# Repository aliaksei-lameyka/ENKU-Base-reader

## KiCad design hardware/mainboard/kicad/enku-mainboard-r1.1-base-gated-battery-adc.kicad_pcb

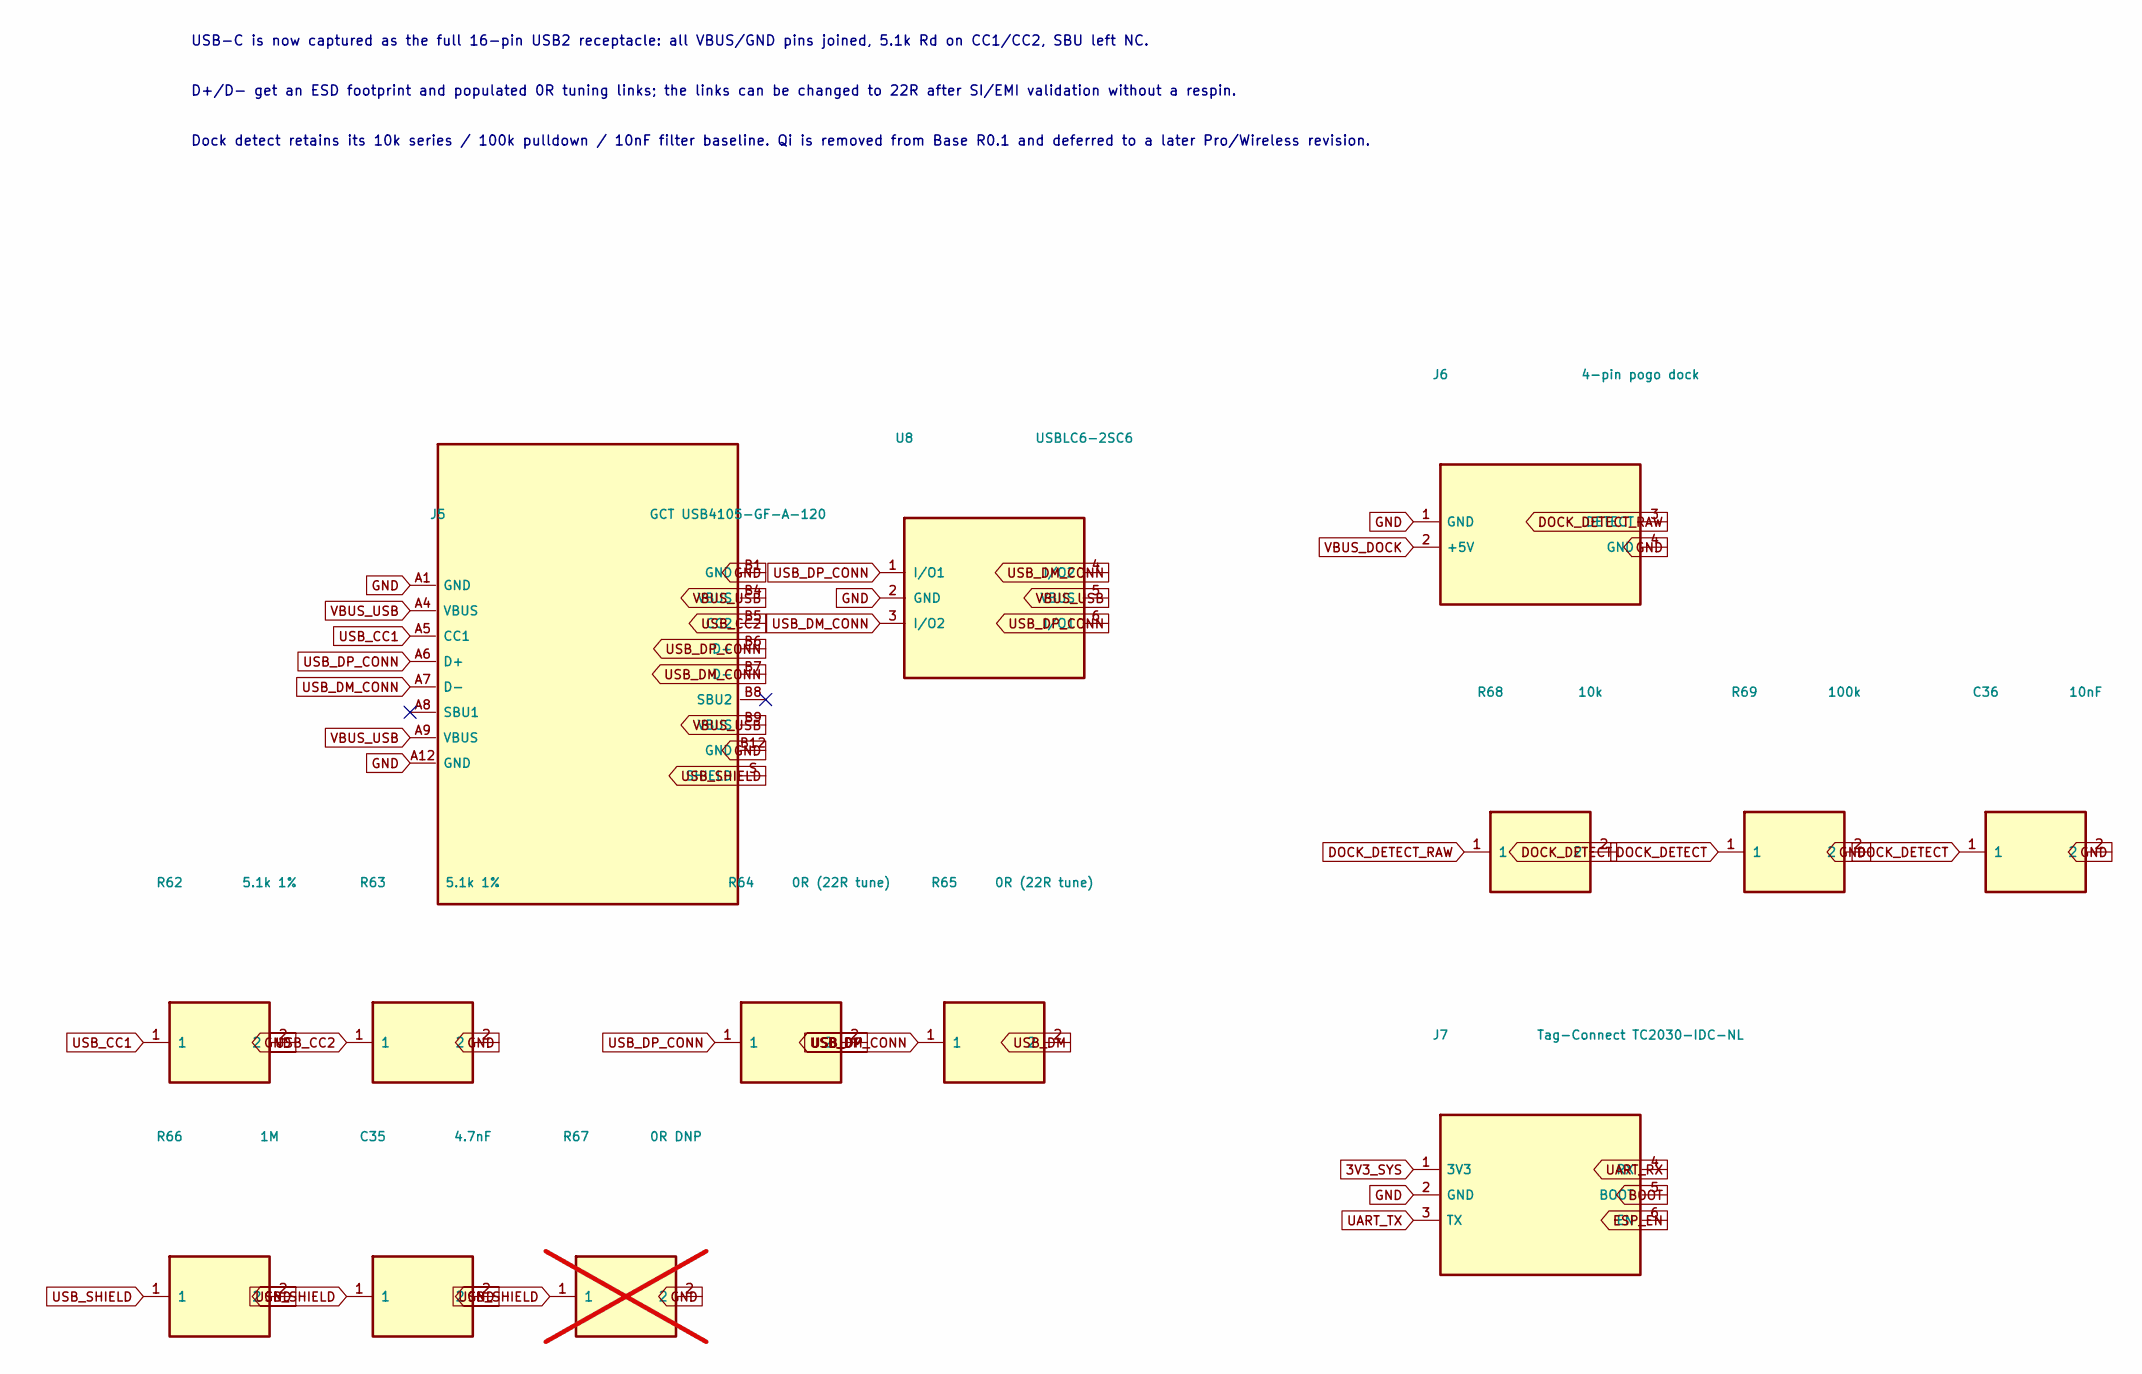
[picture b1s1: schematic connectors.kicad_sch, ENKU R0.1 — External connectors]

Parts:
C35: 4.7nF; C_0603_1608Metric
C36: 10nF; C_0603_1608Metric
J5: GCT USB4105-GF-A-120; USB_C_Receptacle_GCT_USB4105-xx-A_16P_TopMnt_Horizontal
J6: 4-pin pogo dock; DOCK_POGO_4
J7: Tag-Connect TC2030-IDC-NL; Tag-Connect_TC2030-IDC-NL_2x03_P1.27mm_Vertical
R62, R63: 5.1k 1%; R_0603_1608Metric
R64, R65: 0R (22R tune); R_0603_1608Metric
R66: 1M; R_0603_1608Metric
R67: 0R DNP; R_0603_1608Metric; not fitted
R68: 10k; R_0603_1608Metric
R69: 100k; R_0603_1608Metric
U8: USBLC6-2SC6; SOT-23-6

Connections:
3V3_SYS: J7.1 (3V3); also elsewhere on the board
BOOT: J7.5 (BOOT); also elsewhere on the board
DOCK_DETECT: C36.1, R68.2, R69.1; also elsewhere on the board
DOCK_DETECT_RAW: J6.3 (DETECT), R68.1
ESP_EN: J7.6 (EN); also elsewhere on the board
GND: C35.2, C36.2, J5.A1 (GND), J5.A12 (GND), J5.B1 (GND), J5.B12 (GND), J6.1 (GND), J6.4 (GND), J7.2 (GND), R62.2, R63.2, R66.2, R67.2, R69.2, U8.2 (GND); also elsewhere on the board
UART_RX: J7.4 (RX); also elsewhere on the board
UART_TX: J7.3 (TX); also elsewhere on the board
USB_CC1: J5.A5 (CC1), R62.1
USB_CC2: J5.B5 (CC2), R63.1
USB_DM: R65.2; also elsewhere on the board
USB_DM_CONN: J5.A7 (D-), J5.B7 (D-), R65.1, U8.3 (I/O2), U8.4 (I/O2)
USB_DP: R64.2; also elsewhere on the board
USB_DP_CONN: J5.A6 (D+), J5.B6 (D+), R64.1, U8.1 (I/O1), U8.6 (I/O1)
USB_SHIELD: C35.1, J5.S (SHIELD), R66.1, R67.1
VBUS_DOCK: J6.2 (+5V); also elsewhere on the board
VBUS_USB: J5.A4 (VBUS), J5.A9 (VBUS), J5.B4 (VBUS), J5.B9 (VBUS), U8.5 (VBUS); also elsewhere on the board

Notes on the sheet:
USB-C is now captured as the full 16-pin USB2 receptacle: all VBUS/GND pins joined, 5.1k Rd on CC1/CC2, SBU left NC.
D+/D- get an ESD footprint and populated 0R tuning links; the links can be changed to 22R after SI/EMI validation without a respin.
Dock detect retains its 10k series / 100k pulldown / 10nF filter baseline. Qi is removed from Base R0.1 and deferred to a later Pro/Wireless revision.

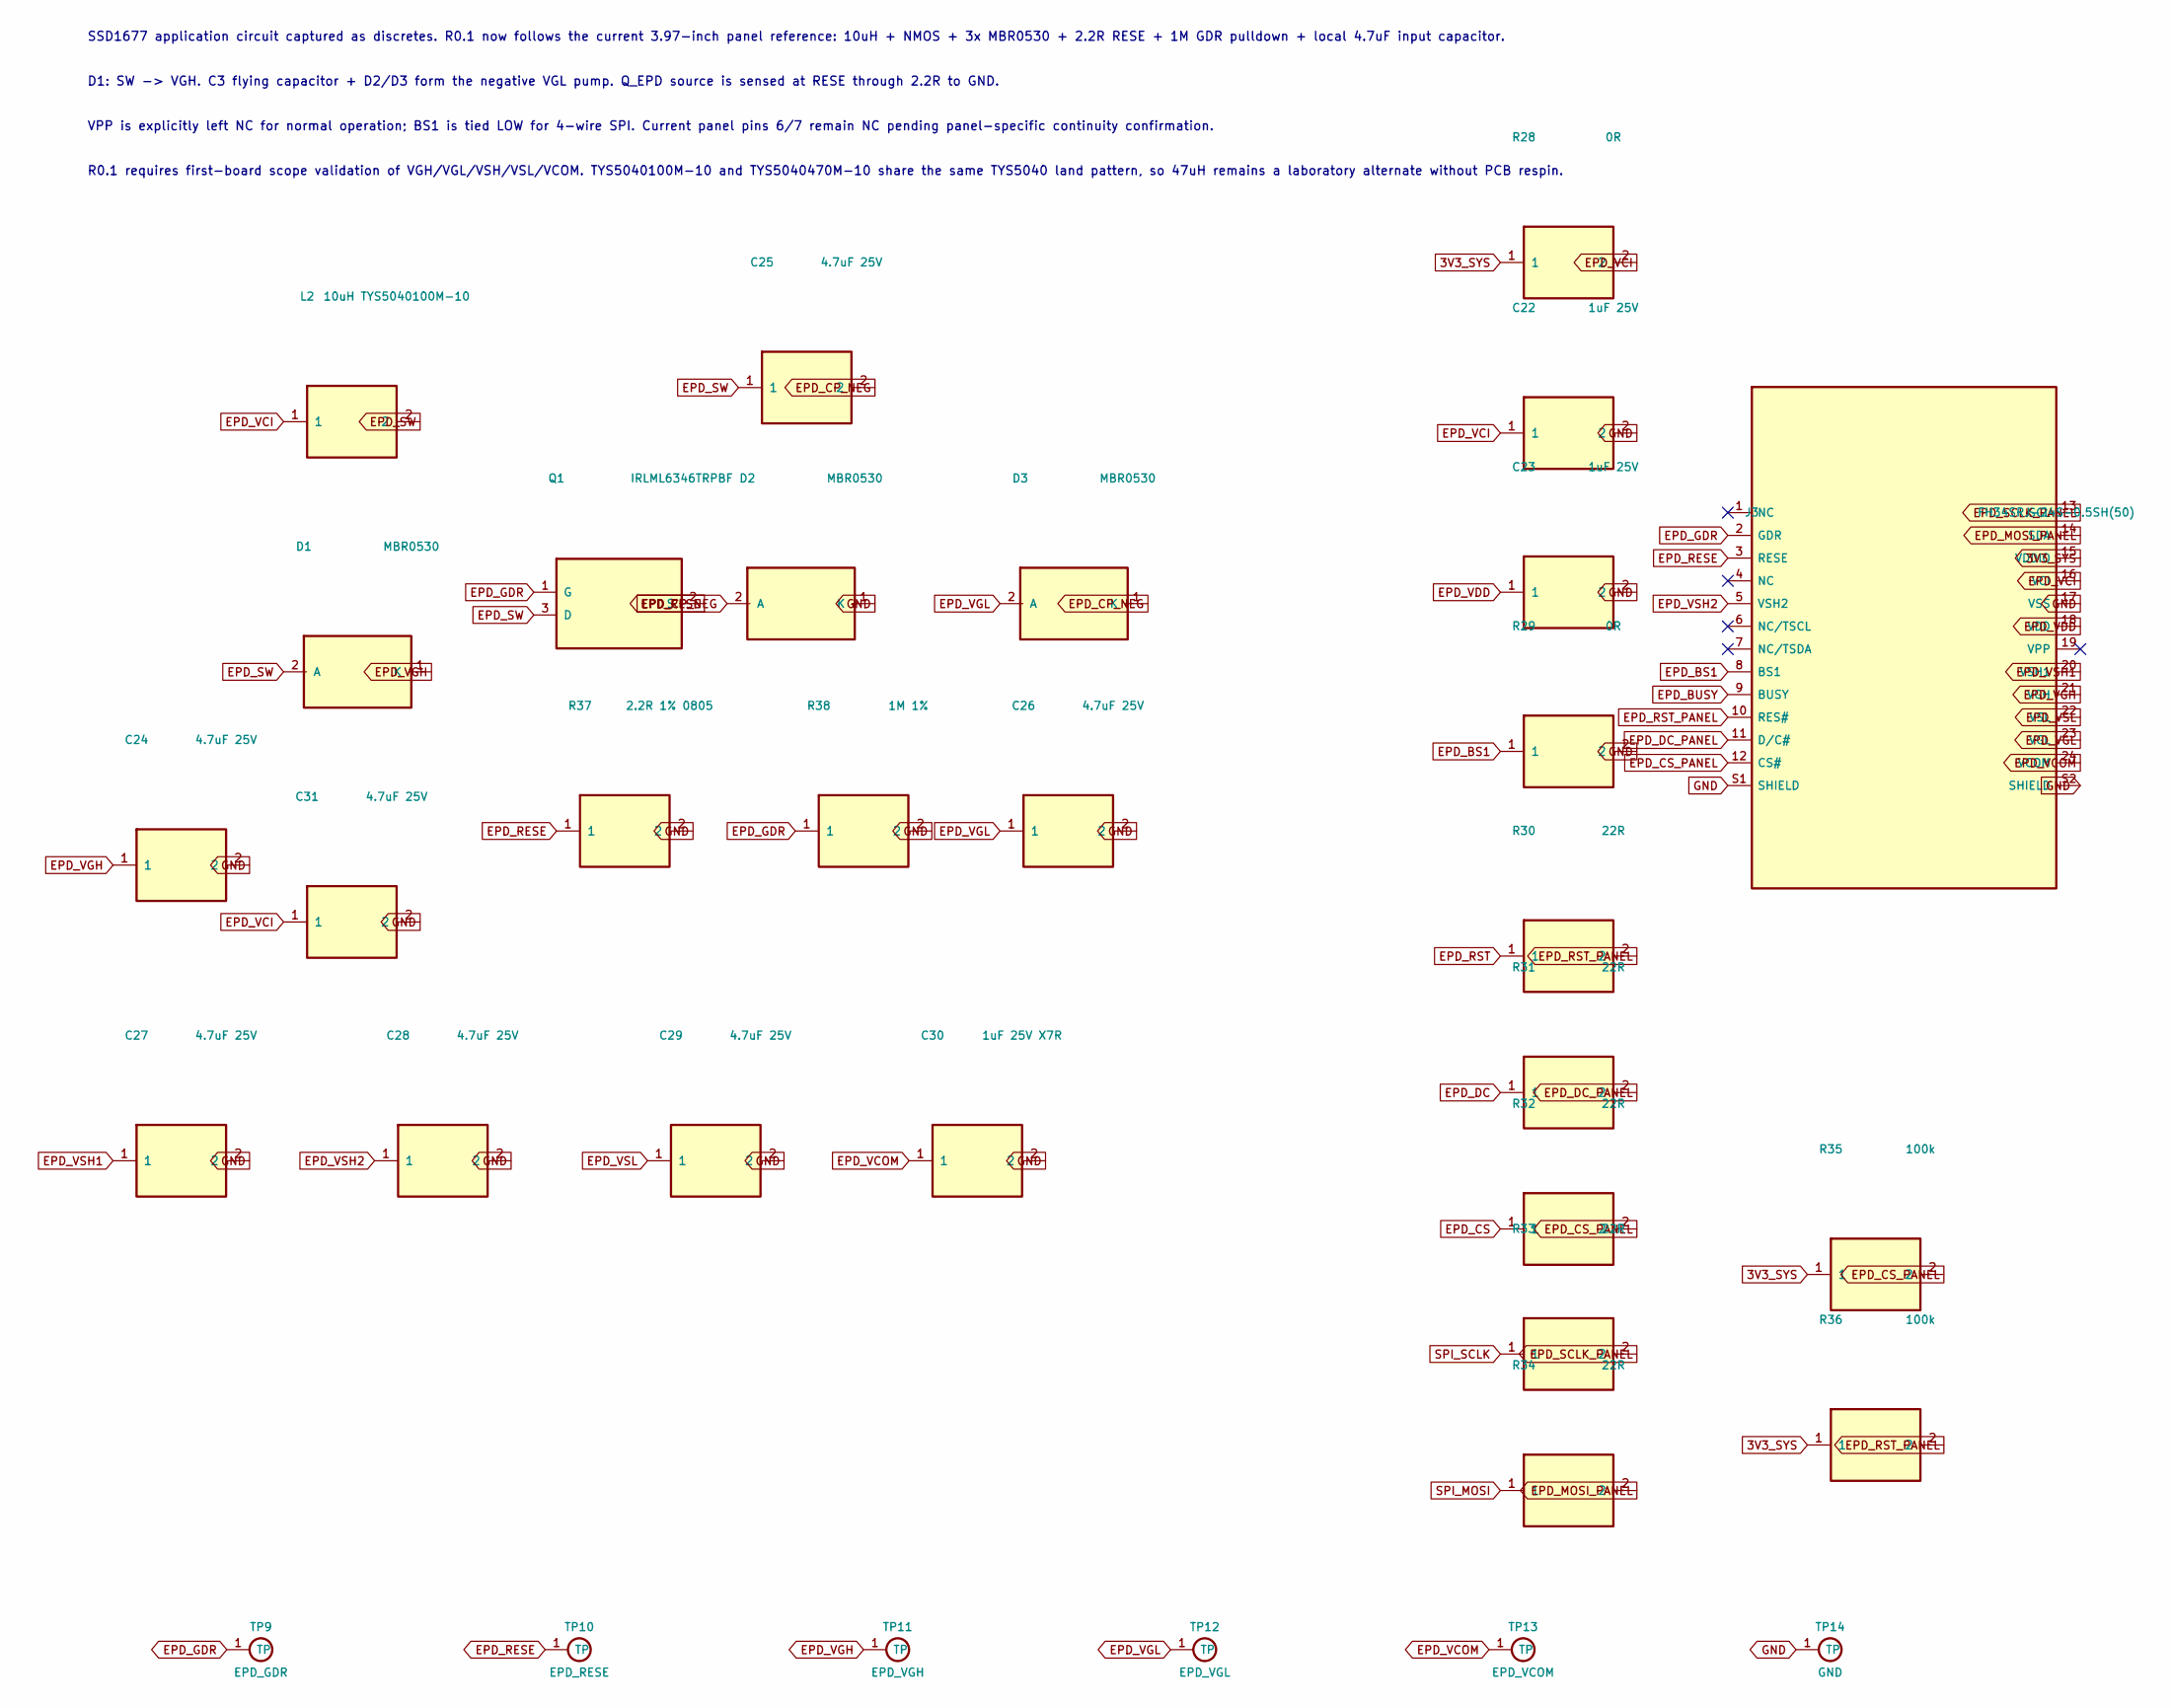
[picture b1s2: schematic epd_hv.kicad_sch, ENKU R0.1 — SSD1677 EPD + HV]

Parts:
C22, C23: 1uF 25V; C_0603_1608Metric
C24, C25, C26, C27, C28, C29, C31: 4.7uF 25V; C_0805_2012Metric
C30: 1uF 25V X7R; C_0805_2012Metric
D1, D2, D3: MBR0530; D_SOD-123
J3: FH34SRJ-24S-0.5SH(50); FH34SRJ-24S-0.5SH
L2: 10uH TYS5040100M-10; TYS5040_5x5
Q1: IRLML6346TRPBF; SOT-23
R28, R29: 0R; R_0603_1608Metric
R30, R31, R32, R33, R34: 22R; R_0603_1608Metric
R35, R36: 100k; R_0603_1608Metric
R37: 2.2R 1% 0805; R_0805_2012Metric
R38: 1M 1%; R_0603_1608Metric
TP9: EPD_GDR; TestPoint_Pad_D1.5mm
TP10: EPD_RESE; TestPoint_Pad_D1.5mm
TP11: EPD_VGH; TestPoint_Pad_D1.5mm
TP12: EPD_VGL; TestPoint_Pad_D1.5mm
TP13: EPD_VCOM; TestPoint_Pad_D1.5mm
TP14: GND; TestPoint_Pad_D1.5mm

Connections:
3V3_SYS: J3.15 (VDDIO), R28.1, R35.1, R36.1; also elsewhere on the board
EPD_BS1: J3.8 (BS1), R29.1
EPD_BUSY: J3.9 (BUSY); also elsewhere on the board
EPD_CP_NEG: C25.2, D2.2 (A), D3.1 (K)
EPD_CS: R32.1; also elsewhere on the board
EPD_CS_PANEL: J3.12 (CS#), R32.2, R35.2
EPD_DC: R31.1; also elsewhere on the board
EPD_DC_PANEL: J3.11 (D/C#), R31.2
EPD_GDR: J3.2 (GDR), Q1.1 (G), R38.1, TP9.1
EPD_MOSI_PANEL: J3.14 (SDA), R34.2
EPD_RESE: J3.3 (RESE), Q1.2 (S), R37.1, TP10.1
EPD_RST: R30.1; also elsewhere on the board
EPD_RST_PANEL: J3.10 (RES#), R30.2, R36.2
EPD_SCLK_PANEL: J3.13 (SCL), R33.2
EPD_SW: C25.1, D1.2 (A), L2.2, Q1.3 (D)
EPD_VCI: C22.1, C31.1, J3.16 (VCI), L2.1, R28.2
EPD_VCOM: C30.1, J3.24 (VCOM), TP13.1
EPD_VDD: C23.1, J3.18 (VDD)
EPD_VGH: C24.1, D1.1 (K), J3.21 (VGH), TP11.1
EPD_VGL: C26.1, D3.2 (A), J3.23 (VGL), TP12.1
EPD_VSH1: C27.1, J3.20 (VSH1)
EPD_VSH2: C28.1, J3.5 (VSH2)
EPD_VSL: C29.1, J3.22 (VSL)
GND: C22.2, C23.2, C24.2, C26.2, C27.2, C28.2, C29.2, C30.2, C31.2, D2.1 (K), J3.17 (VSS), J3.S1 (SHIELD), J3.S2 (SHIELD), R29.2, R37.2, R38.2, TP14.1; also elsewhere on the board
SPI_MOSI: R34.1; also elsewhere on the board
SPI_SCLK: R33.1; also elsewhere on the board

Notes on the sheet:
SSD1677 application circuit captured as discretes. R0.1 now follows the current 3.97-inch panel reference: 10uH + NMOS + 3x MBR0530 + 2.2R RESE + 1M GDR pulldown + local 4.7uF input capacitor.
D1: SW -> VGH. C3 flying capacitor + D2/D3 form the negative VGL pump. Q_EPD source is sensed at RESE through 2.2R to GND.
VPP is explicitly left NC for normal operation; BS1 is tied LOW for 4-wire SPI. Current panel pins 6/7 remain NC pending panel-specific continuity confirmation.
R0.1 requires first-board scope validation of VGH/VGL/VSH/VSL/VCOM. TYS5040100M-10 and TYS5040470M-10 share the same TYS5040 land pattern, so 47uH remains a laboratory alternate without PCB respin.

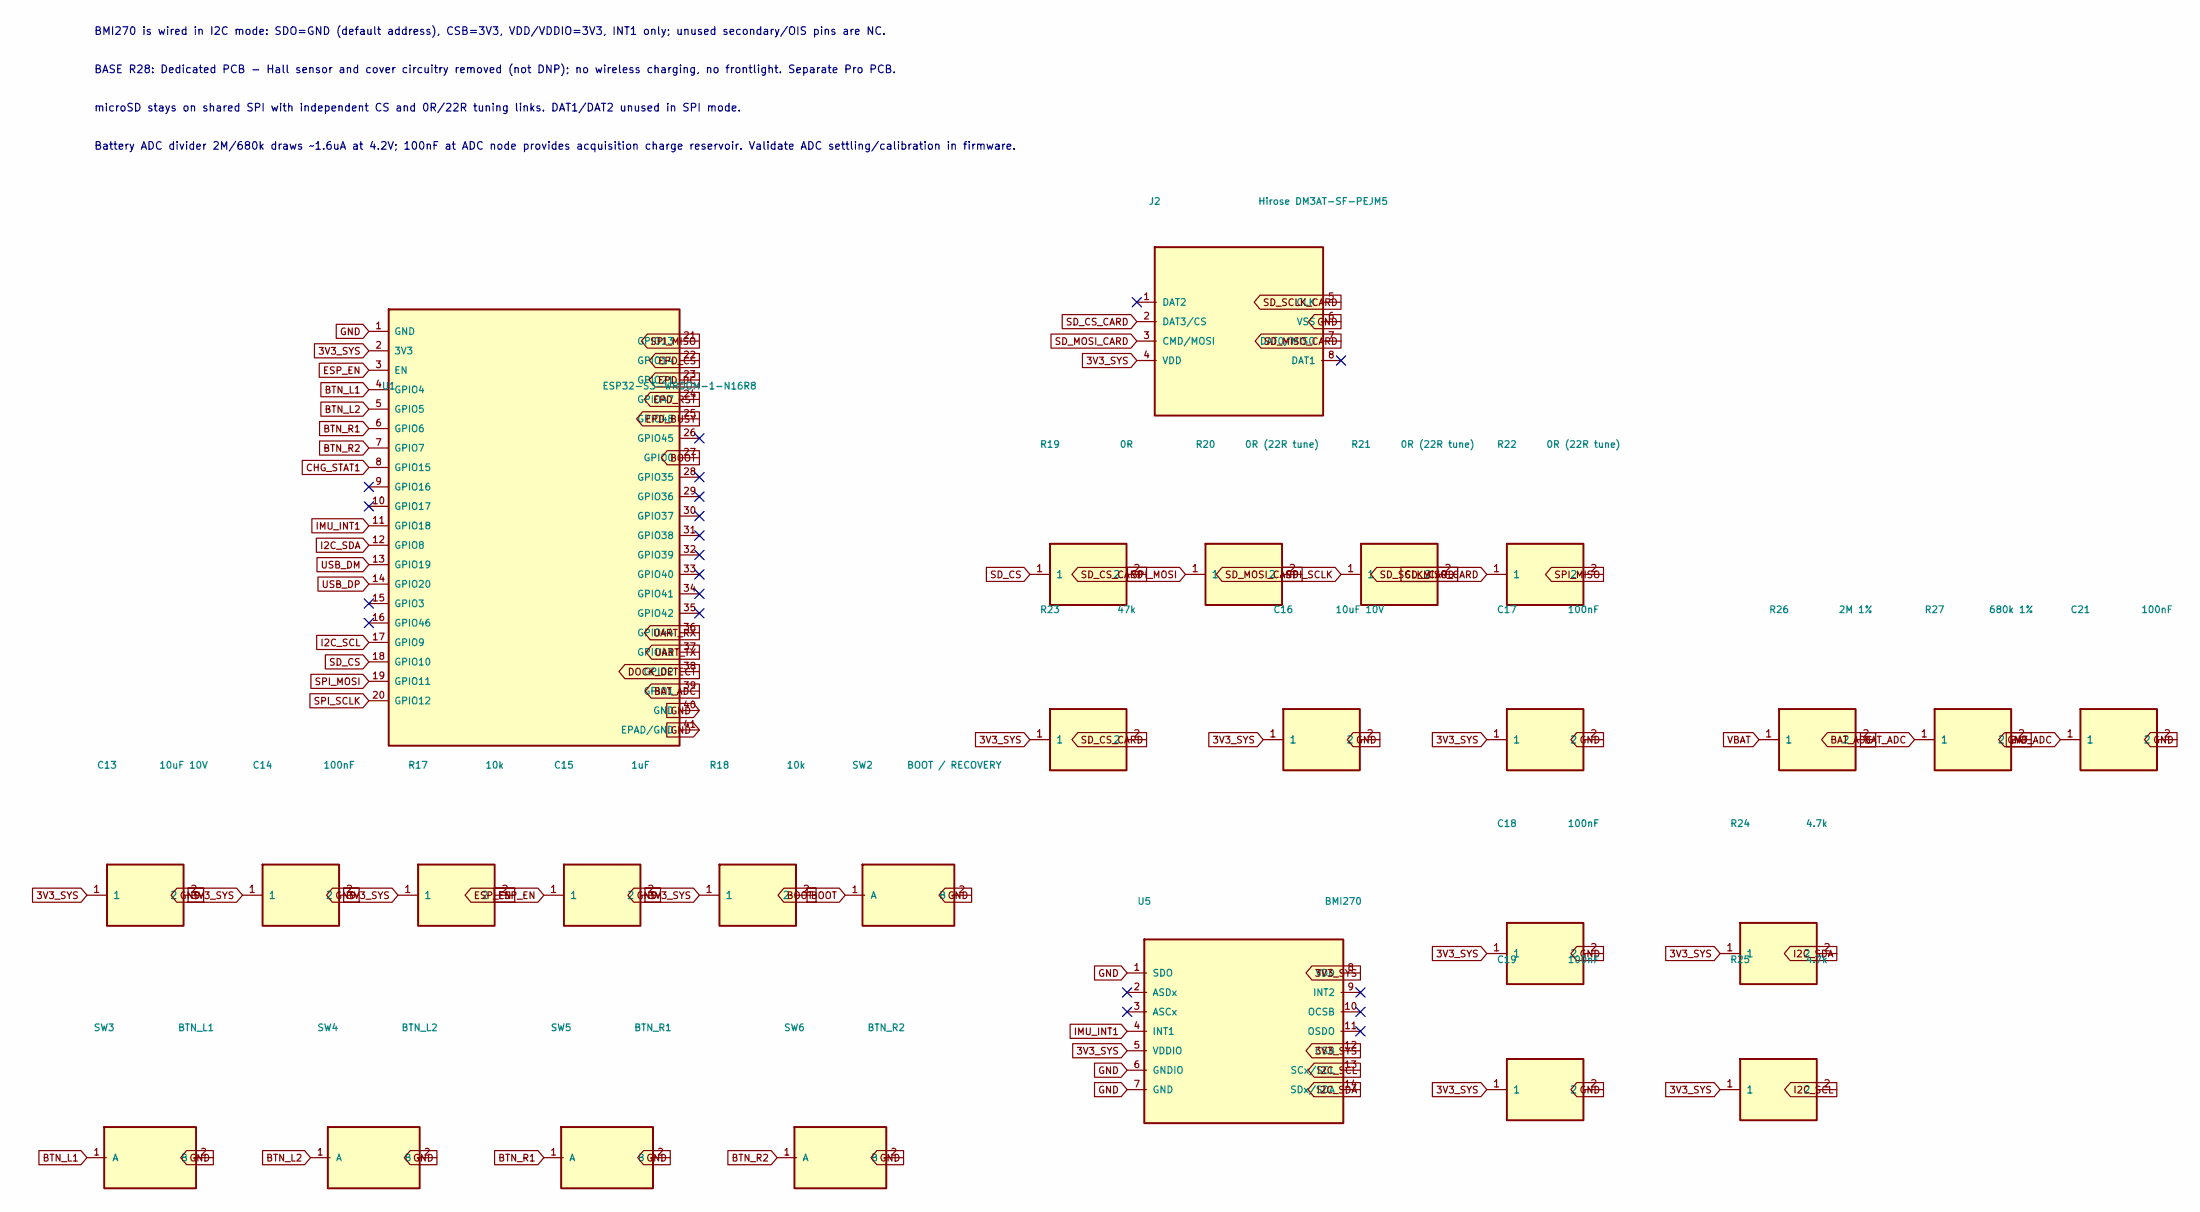
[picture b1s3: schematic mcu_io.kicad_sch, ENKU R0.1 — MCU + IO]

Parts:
C13, C16: 10uF 10V; C_0805_2012Metric
C14, C17, C18, C19, C21: 100nF; C_0603_1608Metric
C15: 1uF; C_0603_1608Metric
J2: Hirose DM3AT-SF-PEJM5; MICROSD_DM3AT_ENKU
R17, R18: 10k; R_0603_1608Metric
R19: 0R; R_0603_1608Metric
R20, R21, R22: 0R (22R tune); R_0603_1608Metric
R23: 47k; R_0603_1608Metric
R24, R25: 4.7k; R_0603_1608Metric
R26: 2M 1%; R_0603_1608Metric
R27: 680k 1%; R_0603_1608Metric
SW2: BOOT / RECOVERY; SW_SPST_TL3342
SW3: BTN_L1; READING_BUTTON_PLACEMENT
SW4: BTN_L2; READING_BUTTON_PLACEMENT
SW5: BTN_R1; READING_BUTTON_PLACEMENT
SW6: BTN_R2; READING_BUTTON_PLACEMENT
U1: ESP32-S3-WROOM-1-N16R8; ESP32-S3-WROOM-1
U5: BMI270; BMI270_Bosch_LGA14

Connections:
3V3_SYS: C13.1, C14.1, C16.1, C17.1, C18.1, C19.1, J2.4 (VDD), R17.1, R18.1, R23.1, R24.1, R25.1, U1.2 (3V3), U5.5 (VDDIO), U5.8 (VDD), U5.12 (CSB); also elsewhere on the board
BAT_ADC: C21.1, R26.2, R27.1, U1.39 (GPIO1)
BAT_ADC_SW: R26.1; also elsewhere on the board
BOOT: R18.2, SW2.1 (A), U1.27 (GPIO0); also elsewhere on the board
BTN_L1: SW3.1 (A), U1.4 (GPIO4)
BTN_L2: SW4.1 (A), U1.5 (GPIO5)
BTN_R1: SW5.1 (A), U1.6 (GPIO6)
BTN_R2: SW6.1 (A), U1.7 (GPIO7)
CHG_STAT1: U1.8 (GPIO15); also elsewhere on the board
DOCK_DETECT: U1.38 (GPIO2); also elsewhere on the board
EPD_BUSY: U1.25 (GPIO48); also elsewhere on the board
EPD_CS: U1.22 (GPIO14); also elsewhere on the board
EPD_DC: U1.23 (GPIO21); also elsewhere on the board
EPD_RST: U1.24 (GPIO47); also elsewhere on the board
ESP_EN: C15.1, R17.2, U1.3 (EN); also elsewhere on the board
GND: C13.2, C14.2, C15.2, C16.2, C17.2, C18.2, C19.2, C21.2, J2.6 (VSS), R27.2, SW2.2 (B), SW3.2 (B), SW4.2 (B), SW5.2 (B), SW6.2 (B), U1.1 (GND), U1.40 (GND), U1.41 (EPAD/GND), U5.1 (SDO), U5.6 (GNDIO), U5.7 (GND); also elsewhere on the board
I2C_SCL: R25.2, U1.17 (GPIO9), U5.13 (SCx/SCL)
I2C_SDA: R24.2, U1.12 (GPIO8), U5.14 (SDx/SDA)
IMU_INT1: U1.11 (GPIO18), U5.4 (INT1)
SD_CS: R19.1, U1.18 (GPIO10)
SD_CS_CARD: J2.2 (DAT3/CS), R19.2, R23.2
SD_MISO_CARD: J2.7 (DAT0/MISO), R22.1
SD_MOSI_CARD: J2.3 (CMD/MOSI), R20.2
SD_SCLK_CARD: J2.5 (CLK), R21.2
SPI_MISO: R22.2, U1.21 (GPIO13)
SPI_MOSI: R20.1, U1.19 (GPIO11); also elsewhere on the board
SPI_SCLK: R21.1, U1.20 (GPIO12); also elsewhere on the board
UART_RX: U1.36 (GPIO44); also elsewhere on the board
UART_TX: U1.37 (GPIO43); also elsewhere on the board
USB_DM: U1.13 (GPIO19); also elsewhere on the board
USB_DP: U1.14 (GPIO20); also elsewhere on the board

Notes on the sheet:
BMI270 is wired in I2C mode: SDO=GND (default address), CSB=3V3, VDD/VDDIO=3V3, INT1 only; unused secondary/OIS pins are NC.
BASE R28: Dedicated PCB - Hall sensor and cover circuitry removed (not DNP); no wireless charging, no frontlight. Separate Pro PCB.
microSD stays on shared SPI with independent CS and 0R/22R tuning links. DAT1/DAT2 unused in SPI mode.
Battery ADC divider 2M/680k draws ~1.6uA at 4.2V; 100nF at ADC node provides acquisition charge reservoir. Validate ADC settling/calibration in firmware.

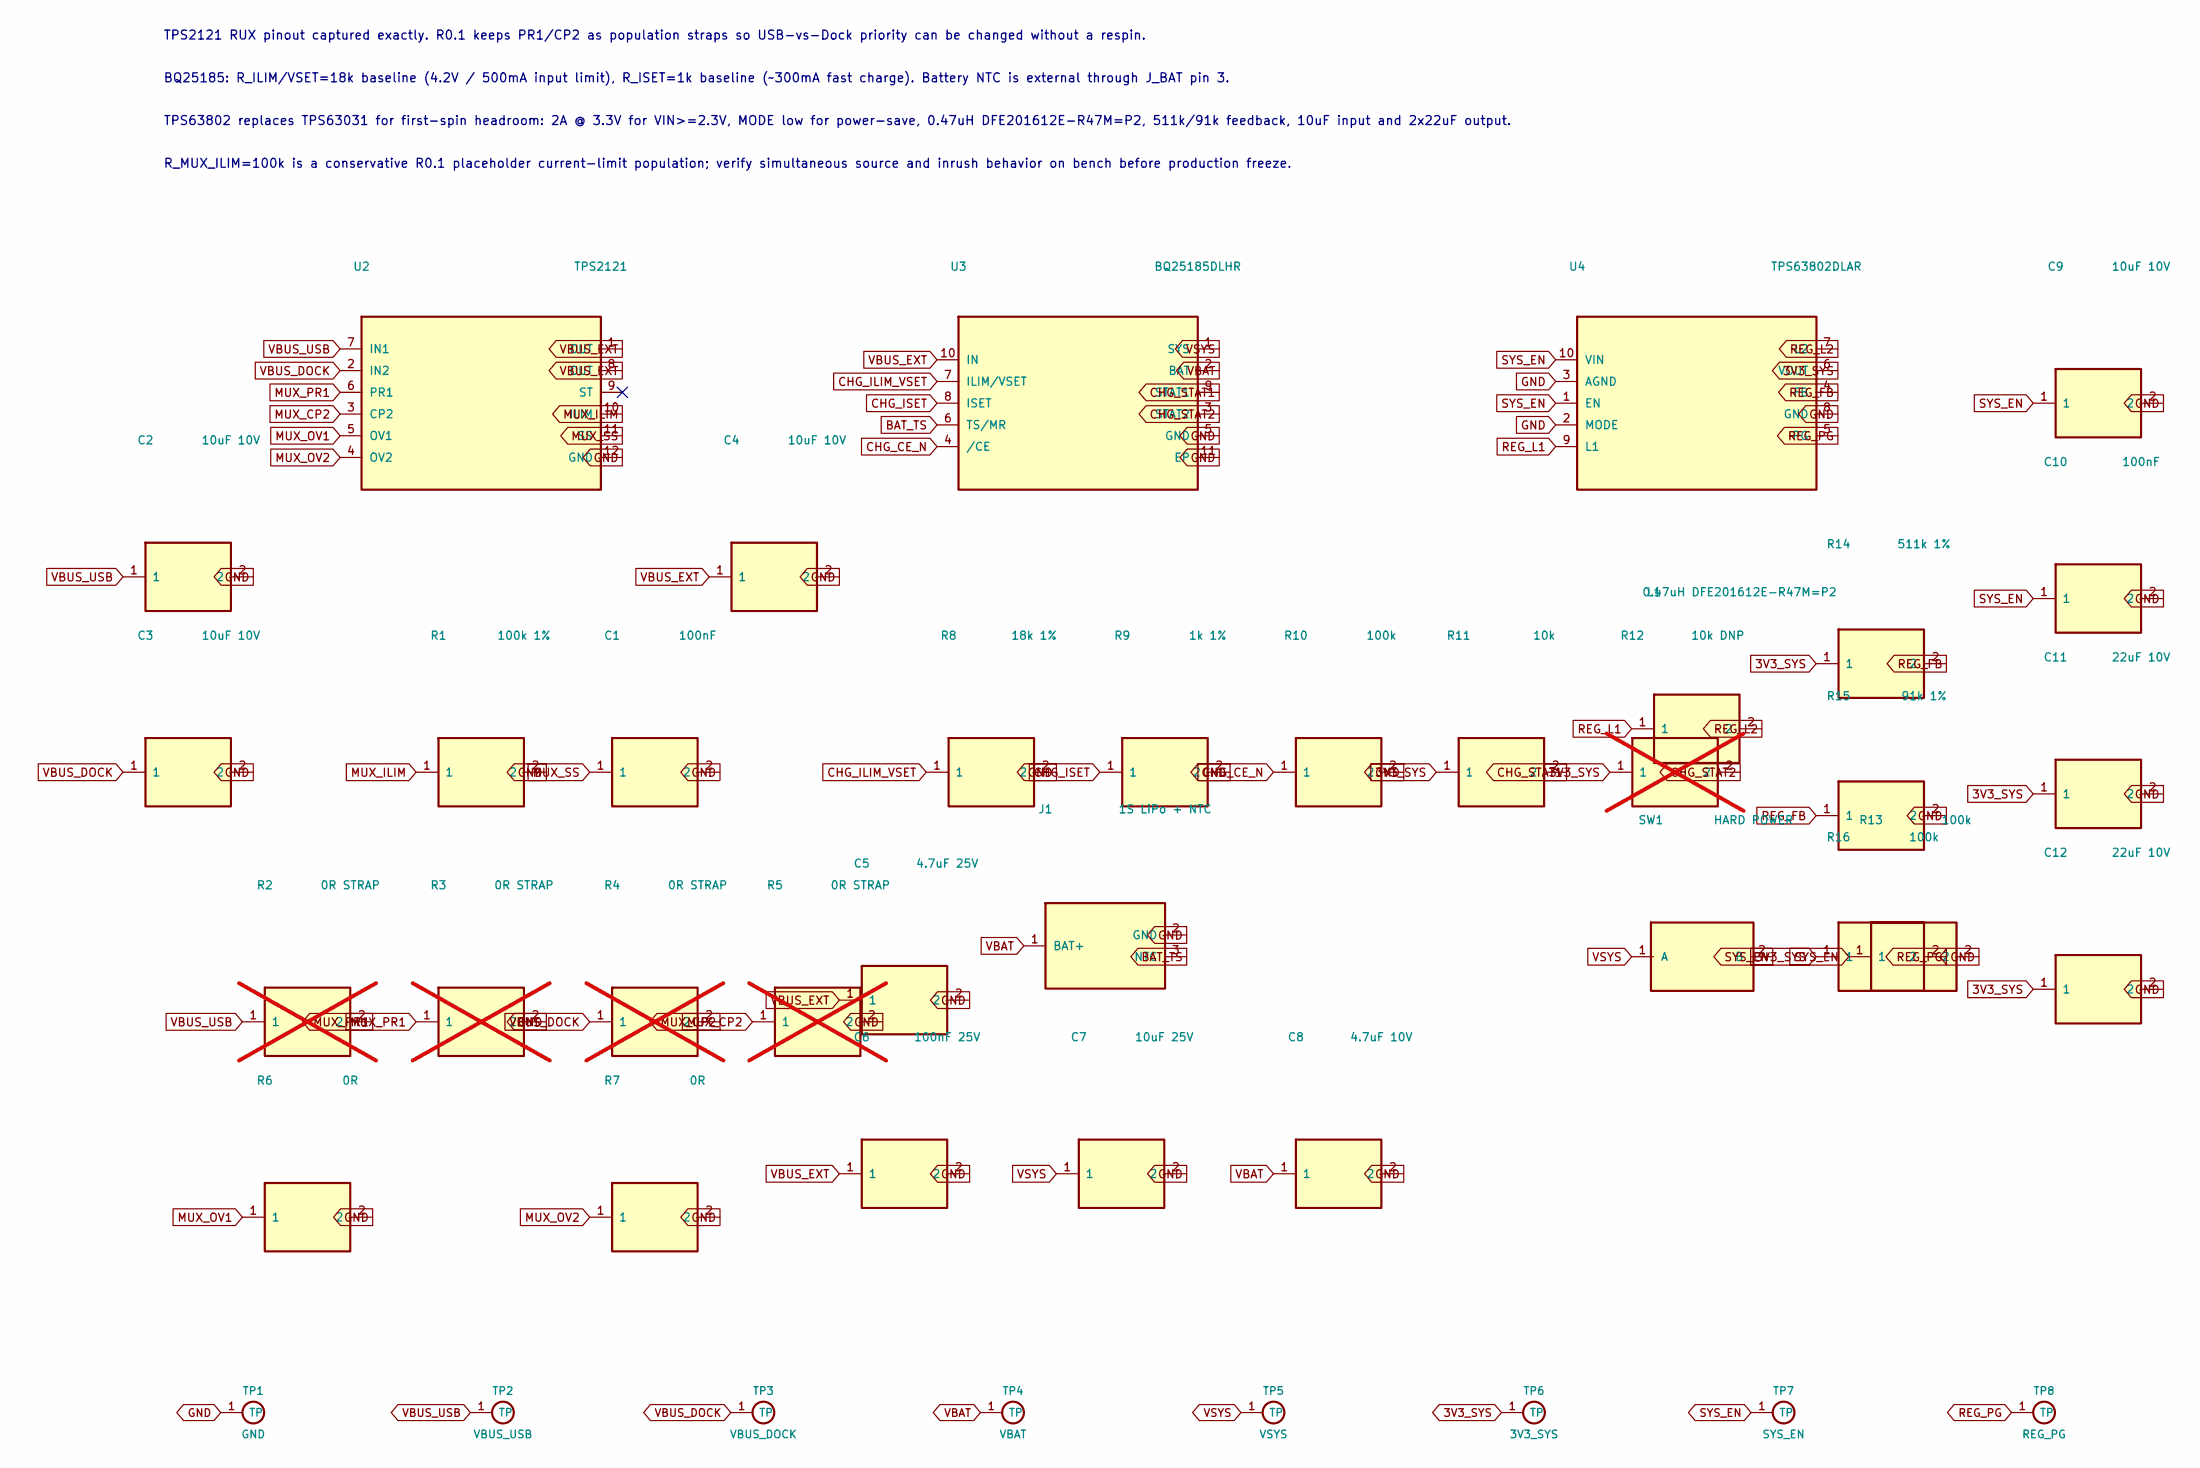
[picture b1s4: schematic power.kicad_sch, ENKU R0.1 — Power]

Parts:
C1, C10: 100nF; C_0603_1608Metric
C2, C3, C4, C9: 10uF 10V; C_0805_2012Metric
C5: 4.7uF 25V; C_0805_2012Metric
C6: 100nF 25V; C_0603_1608Metric
C7: 10uF 25V; C_0805_2012Metric
C8: 4.7uF 10V; C_0805_2012Metric
C11, C12: 22uF 10V; C_0805_2012Metric
J1: 1S LiPo + NTC; JST_PH_S3B-PH-SM4-TB_1x03-1MP_P2.00mm_Horizontal
L1: 0.47uH DFE201612E-R47M=P2; Murata_DFE201612E
R1: 100k 1%; R_0603_1608Metric
R2, R3, R4, R5: 0R STRAP; R_0603_1608Metric; not fitted
R6, R7: 0R; R_0603_1608Metric
R8: 18k 1%; R_0603_1608Metric
R9: 1k 1%; R_0603_1608Metric
R10, R13, R16: 100k; R_0603_1608Metric
R11: 10k; R_0603_1608Metric
R12: 10k DNP; R_0603_1608Metric; not fitted
R14: 511k 1%; R_0603_1608Metric
R15: 91k 1%; R_0603_1608Metric
SW1: HARD POWER; HARD_POWER_SWITCH_PLACEMENT
TP1: GND; TestPoint_Pad_D1.5mm
TP2: VBUS_USB; TestPoint_Pad_D1.5mm
TP3: VBUS_DOCK; TestPoint_Pad_D1.5mm
TP4: VBAT; TestPoint_Pad_D1.5mm
TP5: VSYS; TestPoint_Pad_D1.5mm
TP6: 3V3_SYS; TestPoint_Pad_D1.5mm
TP7: SYS_EN; TestPoint_Pad_D1.5mm
TP8: REG_PG; TestPoint_Pad_D1.5mm
U2: TPS2121; TPS2121_RUX0012A
U3: BQ25185DLHR; BQ25185_DLH0010A
U4: TPS63802DLAR; TPS63802_DLA0010A

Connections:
3V3_SYS: C11.1, C12.1, R11.1, R12.1, R14.1, R16.1, TP6.1, U4.6 (VOUT); also elsewhere on the board
BAT_TS: J1.3 (NTC), U3.6 (TS/MR)
CHG_CE_N: R10.1, U3.4 (/CE)
CHG_ILIM_VSET: R8.1, U3.7 (ILIM/VSET)
CHG_ISET: R9.1, U3.8 (ISET)
CHG_STAT1: R11.2, U3.9 (STAT1); also elsewhere on the board
CHG_STAT2: R12.2, U3.3 (STAT2)
GND: C1.2, C2.2, C3.2, C4.2, C5.2, C6.2, C7.2, C8.2, C9.2, C10.2, C11.2, C12.2, J1.2 (GND), R1.2, R3.2, R5.2, R6.2, R7.2, R8.2, R9.2, R10.2, R13.2, R15.2, TP1.1, U2.12 (GND), U3.5 (GND), U3.11 (EP), U4.2 (MODE), U4.3 (AGND), U4.8 (GND); also elsewhere on the board
MUX_CP2: R4.2, R5.1, U2.3 (CP2)
MUX_ILIM: R1.1, U2.10 (ILIM)
MUX_OV1: R6.1, U2.5 (OV1)
MUX_OV2: R7.1, U2.4 (OV2)
MUX_PR1: R2.2, R3.1, U2.6 (PR1)
MUX_SS: C1.1, U2.11 (SS)
REG_FB: R14.2, R15.1, U4.4 (FB)
REG_L1: L1.1, U4.9 (L1)
REG_L2: L1.2, U4.7 (L2)
REG_PG: R16.2, TP8.1, U4.5 (PG)
SYS_EN: C9.1, C10.1, R13.1, SW1.2 (B), TP7.1, U4.1 (EN), U4.10 (VIN)
VBAT: C8.1, J1.1 (BAT+), TP4.1, U3.2 (BAT); also elsewhere on the board
VBUS_DOCK: C3.1, R4.1, TP3.1, U2.2 (IN2); also elsewhere on the board
VBUS_EXT: C4.1, C5.1, C6.1, U2.1 (OUT), U2.8 (OUT), U3.10 (IN)
VBUS_USB: C2.1, R2.1, TP2.1, U2.7 (IN1); also elsewhere on the board
VSYS: C7.1, SW1.1 (A), TP5.1, U3.1 (SYS)

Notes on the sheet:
TPS2121 RUX pinout captured exactly. R0.1 keeps PR1/CP2 as population straps so USB-vs-Dock priority can be changed without a respin.
BQ25185: R_ILIM/VSET=18k baseline (4.2V / 500mA input limit), R_ISET=1k baseline (~300mA fast charge). Battery NTC is external through J_BAT pin 3.
TPS63802 replaces TPS63031 for first-spin headroom: 2A @ 3.3V for VIN>=2.3V, MODE low for power-save, 0.47uH DFE201612E-R47M=P2, 511k/91k feedback, 10uF input and 2x22uF output.
R_MUX_ILIM=100k is a conservative R0.1 placeholder current-limit population; verify simultaneous source and inrush behavior on bench before production freeze.
